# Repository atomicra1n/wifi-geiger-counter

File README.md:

# Wi-Fi Geiger Counter

A DIY Geiger counter PCB which can detect ionizing radiation and log readings over Wi-Fi. Built with an ESP32, and a HV multiplier circuit that steps up 3.7V to 400V for the GM tube.

## Features

- M4011/SBM-20 Geiger tube with pulse detection (tuned for M4011)
- Custom HV circuit (around 400V) with a single LiPo cell
- Wi-Fi data logging with a dashboard and a JSON API
- Buzzer with clicking on each count
- USB-C charging
- ESD and overvoltage protection

## Motivation
I made this project as I already own a FNIRSI GC-01 Geiger Counter, but I've always been intrigued by how they work and wanted to have a crack at making my own. It was an interesting challenge, especially given the difficulties around handling 400 volts, clearance, etc. Additionally, given the addition of Wi-Fi compared to the GC-01, I can log data from anywhere (the GC-01 requires a constant USB-C connection).

## Functionality
- Power from USB-C goes into a TP4056 which charges the LiPo battery. An AP2112K reduces the voltage from the battery to 3.3V to be safe for the ESP32.
- ESP32 uses PWM on a MMBTA42 transistor which switches an inductor, it ramps up to 200V-ish and then a diode + capacitor voltage doubler ups that to around 400V.
- A 100Megaohm/220kiloohm resistor divider reduces the 400V down to around 0.88, which is read by the ESP32 via its ADC and PID in the firmware adjusts to continuously hold at 400V.
- When the M4011 tube detects decay, the pulse enters a transistor and it is turned into a 3.3V signal for the ESP32 which is counted and clicks the buzzer.
- The firmware tallies counts over 60 seconds to calculate a CPM and converts into micro Sv/h via the configured conversion factor. ESP32 hosts a small web page and a JSON endpoint.

## How it was made
This is my first project in KiCad, so I had to figure it out for the most part. I picked the parts on LCSC and imported them, sketched the HV circuit on paper and then built it step by step. A few issues I ran into:
- I configured net class patterns to keep HV clearance, but I misconfigured them (set to HV instead of /HV) and they were ignored. As such, when I thought I was done, none of my rules were actually checked.
- My USB TVS diode was wired the wrong way which would short VBUS. I swapped it for a bidirectional one.
- My status LED was backwards and improperly wired, so I changed it to stay high on boot.
- The USB-C connector was facing inside the board instead of outside, very easy mistake to make in the PCB editor! Had to rotate and reroute completely.
- The buzzer footprint didn't match my actual part, so I had to find the right one on LCSC and reimport it.
- The ADC reading was wrong by around 30% in the firmware, so I fixed it by using the calibrated ADC reading in MicroPython

## Tech stack
- KiCad for the PCB design
- MicroPython for the ESP32 firmware
- JLCPCB for the board and LCSC for parts

## Repo layout
- pcb/ contains the actual KiCad project
- pcb/gerbers contain the gerber and drill files
- pcb/cpl/ contains the component positions
- firmware/ contains the MicroPython code
- images/ contains a render of the PCB
- BOM.csv contains the parts list
- JOURNAL.md is the devlog

## Bill of materials

| Part | Qty | Source | Unit | Total |
|---|---|---|---|---|
| [PCB Manufacturing](https://jlcpcb.com) | 1 | JLCPCB | $4.00 | $4.00 |
| [ESP32-C3-MINI](https://www.lcsc.com/product-detail/C2838502.html) | 1 | LCSC | $3.06 | $3.06 |
| [TP4056-42-ESOP8](https://www.lcsc.com/product-detail/C16581.html) | 5 | LCSC | $0.19 | $0.95 |
| [AP2112K-3.3TRG1](https://www.lcsc.com/product-detail/C51118.html) | 5 | LCSC | $0.18 | $0.90 |
| [USBLC6-2SC6](https://www.lcsc.com/product-detail/C7519.html) | 5 | LCSC | $0.18 | $0.90 |
| [MMBTA42](https://www.lcsc.com/product-detail/C94389.html) | 10 | LCSC | $0.05 | $0.50 |
| [MMBT3904](https://www.lcsc.com/product-detail/C242260.html) | 20 | LCSC | $0.04 | $0.80 |
| [US1M](https://www.lcsc.com/product-detail/C81191.html) | 3 | LCSC | $0.05 | $0.15 |
| [1N4148W](https://www.lcsc.com/product-detail/C917030.html) | 50 | LCSC | $0.01 | $0.50 |
| [SMF5.0CA](https://www.lcsc.com/product-detail/C908214.html) | 20 | LCSC | $0.02 | $0.40 |
| [MM3Z3V3](https://www.lcsc.com/product-detail/C52056.html) | 50 | LCSC | $0.02 | $1.00 |
| [Red LED 0805](https://www.lcsc.com/product-detail/C84256.html) | 50 | LCSC | $0.02 | $1.00 |
| [Yellow LED 0805](https://www.lcsc.com/product-detail/C84261.html) | 20 | LCSC | $0.02 | $0.40 |
| [MLT-8530](https://www.lcsc.com/product-detail/C94599.html) | 5 | LCSC | $0.21 | $1.05 |
| [FNR6045S103KT](https://www.lcsc.com/product-detail/C168108.html) | 5 | LCSC | $0.25 | $1.25 |
| [TYPE-C-31-M-12](https://www.lcsc.com/product-detail/C165948.html) | 5 | LCSC | $0.18 | $0.90 |
| [S2B-PH-K-S-GW](https://www.lcsc.com/product-detail/C157932.html) | 5 | LCSC | $0.17 | $0.85 |
| [1k 0805](https://www.lcsc.com/product-detail/C17513.html) | 100 | LCSC | $0.01 | $1.00 |
| [10k 0805](https://www.lcsc.com/product-detail/C17414.html) | 100 | LCSC | $0.01 | $1.00 |
| [5.1k 0805](https://www.lcsc.com/product-detail/C27834.html) | 100 | LCSC | $0.01 | $1.00 |
| [2.2k 0805](https://www.lcsc.com/product-detail/C17520.html) | 100 | LCSC | $0.01 | $1.00 |
| [220k 0805](https://www.lcsc.com/product-detail/C17556.html) | 100 | LCSC | $0.01 | $1.00 |
| [100k 0805](https://www.lcsc.com/product-detail/C17407.html) | 100 | LCSC | $0.01 | $1.00 |
| [4.7M 1206 500V](https://www.lcsc.com/product-detail/C510138.html) | 10 | LCSC | $0.01 | $0.10 |
| [10M 1206](https://www.lcsc.com/product-detail/C2933576.html) | 100 | LCSC | $0.01 | $1.00 |
| [10µF 0805](https://www.lcsc.com/product-detail/C15850.html) | 20 | LCSC | $0.07 | $1.40 |
| [1µF 0805](https://www.lcsc.com/product-detail/C28323.html) | 10 | LCSC | $0.04 | $0.40 |
| [100nF 0805](https://www.lcsc.com/product-detail/C49678.html) | 20 | LCSC | $0.02 | $0.40 |
| [10nF 1kV 1206](https://www.lcsc.com/product-detail/C107192.html) | 20 | LCSC | $0.03 | $0.60 |
| [GM Tube - M4011](https://github.com/SensorsIot/Geiger-Counter-RadiationD-v1.1-CAJOE-/blob/master/M4011%20Geiger%20Tube%20Specification.pdf) | 1 | Salvaged (FNIRSI GC-01) | $0.01 | $0.01 |
| 3.7V LiPo battery | 1 | Salvaged (FNIRSI GC-01) | $0.01 | $0.01 |
| [2.54-1*3P](https://www.lcsc.com/product-detail/C49257.html) | 20 | LCSC | $0.03 | $0.60 |
| **Parts subtotal** | | | | **$29.13** |
| Shipping (estimate) | | | | $25.00 |
| **Total** | | | | **$54.13** |

The Geiger Tube and Battery were salvaged from my GC-01, so they're effectively free. You can buy similar pieces on Ebay, Aliexpress or other stores.

## Assembly
Please keep in mind the board makes around 400V, even though it's low current, it could still inflict a shock, as such, please be careful. Before touching the HV side, I recommend unplugging the USB and battery and shorting C10 to GND to discharge it.

1. Order the PCB from JLCPCB using the gerber files and the parts from LCSC using the BOM.
2. Start with the power section. Solder the USB-C connector, USBLC6, TVS diode, TP4056, AP2112K and their resistors + capacitors. Do not work with the battery yet. Plug in USB-C and verify that the charge LED turns on. You should be getting 3.3V.
3. Solder the ESP32-C3-MINI-1 and the status LED. The ESP32 has pads underneath, so you'll need hot air or a hot plate for it. Flash MicroPython (more below) and check that you get a REPL on the ESP32.
4. Begin the HV supply. Solder Q1, L1, US1M diodes, 10nF 1kV capacitors and the 10 megaohm resistor divider chain but avoid connecting the tube at this point. Run the firmware and see the HV values it prints. I recommend not trying to measure the 400V with a multimeter as the 10 megaohm input can load the circuit.
5. Now for the pulse detection and the buzzer, solder Q2, Q3, the buzzer and the rest.
6. To finish, you can plug your tube into J3 (verify anode and cathode!!!) and connect the battery.

Keep in mind I intentionally avoid populating SW1 (reset) and SW2 (boot) switches for simplicity, but you may do so yourself if you want to (they're excluded from the BOM). If you ever need them, you can short their pads. The ESP32 can be flashed over USB without requiring the boot switch, as you can see below.

## Firmware

1. Start by downloading MicroPython for the ESP32-C3 from [micropython.org](https://micropython.org/download/ESP32_GENERIC_C3/) and flash it:
```sh
pip install esptool
esptool.py --chip esp32c3 erase_flash
esptool.py --chip esp32c3 write_flash -z 0x0 ESP32_GENERIC_C3-<your_version>.bin
```
2. Put your Wi-Fi name and password in firmware/config.py
3. Copy the files over:
```sh
pip install mpremote
cd firmware
mpremote cp config.py geiger.py hv_control.py buzzer.py wifi_manager.py main.py :
mpremote reset
```
4. If all goes well, your IP address should get printed over serial. Try opening it in the browser for the dashboard, or use /api/data for the JSON data.

## AI disclosure
LLMs (Claude Opus 4.6/5.5) was mostly used to get feedback on the schematic, review parts of it, assist in fixing bugs and writing the dashboard in wifi_manager.py. It was also used for other tedious but simple tasks, such as adding the BOM to this README.

---

Built for [Hack Club Half Life](https://halflife.hackclub.com/) 
Week 1 (PCBs).

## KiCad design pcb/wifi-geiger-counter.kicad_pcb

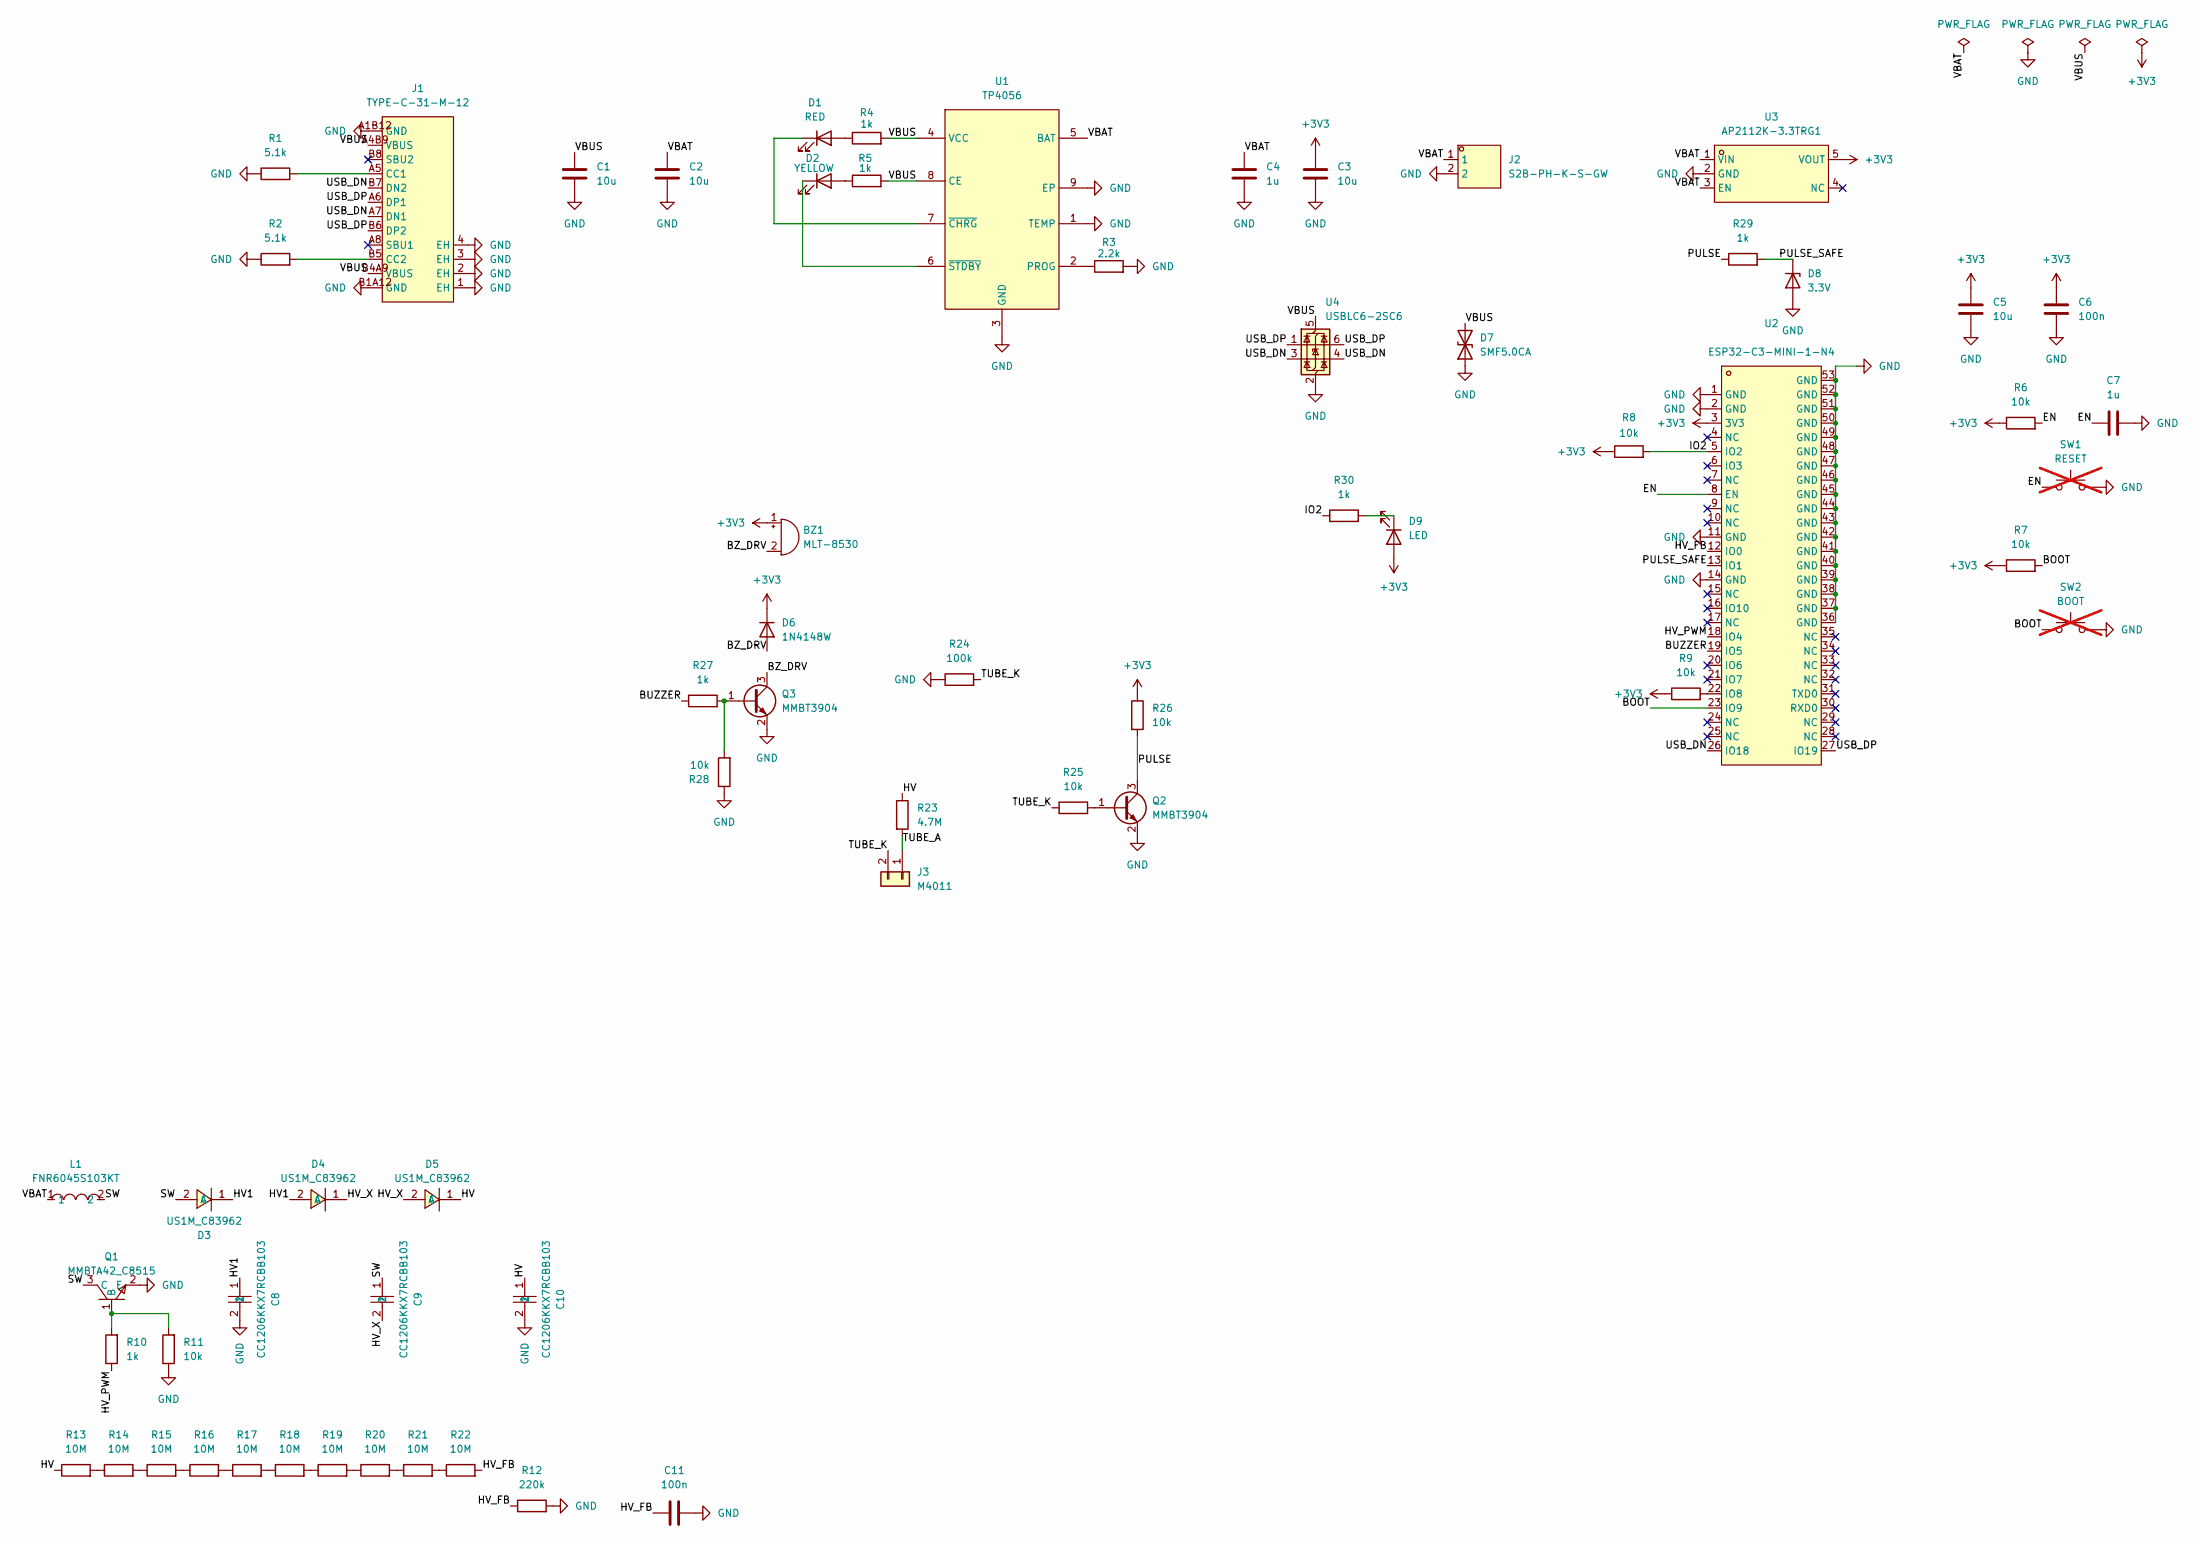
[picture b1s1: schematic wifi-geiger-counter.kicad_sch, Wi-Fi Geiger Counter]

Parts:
BZ1: MLT-8530; BUZ-SMD_4P-L8.5-W8.5-P8.50-BR
C1, C2, C3, C5: 10u; C_0805_2012Metric
C4, C7: 1u; C_0805_2012Metric
C6, C11: 100n; C_0805_2012Metric
C8, C9, C10: CC1206KKX7RCBB103; C1206; MPN CC1206KKX7RCBB103; LCSC Part C107192
D1: RED; LED_0805_2012Metric
D2: YELLOW; LED_0805_2012Metric
D3, D4, D5: US1M_C83962; SMA_L4.3-W2.6-LS5.2-RD; MPN US1M; LCSC Part C83962
D6: 1N4148W; D_SOD-123
D7: SMF5.0CA; D_SOD-123F
D8: 3.3V; D_SOD-323
D9: LED; LED_0805_2012Metric
J1: TYPE-C-31-M-12; USB-C_SMD-TYPE-C-31-M-12_1; MPN TYPE-C-31-M-12; LCSC Part C165948
J2: S2B-PH-K-S-GW; CONN-TH_S2B-PH-K-S-GW; MPN S2B-PH-K-S-GW; LCSC Part C157932
J3: M4011; PinHeader_1x02_P2.54mm_Vertical
L1: FNR6045S103KT; IND-SMD_L6.0-W6.0_FNR60XXS; MPN FNR6045S103KT; LCSC Part C168108
Q1: MMBTA42_C8515; SOT-23-3_L2.9-W1.3-P1.90-LS2.4-BR; MPN MMBTA42(RANGE:100-200); LCSC Part C8515
Q2, Q3: MMBT3904; SOT-23
R1, R2: 5.1k; R_0805_2012Metric
R3: 2.2k; R_0805_2012Metric
R4, R5, R10, R27, R29, R30: 1k; R_0805_2012Metric
R6, R7, R8, R9, R11, R25, R26, R28: 10k; R_0805_2012Metric
R12: 220k; R_0805_2012Metric
R13, R14, R15, R16, R17, R18, R19, R20, R21, R22: 10M; R_1206_3216Metric
R23: 4.7M; R_1206_3216Metric
R24: 100k; R_0805_2012Metric
SW1: RESET; SW_SPST_CK_KMS2xxGP; not fitted
SW2: BOOT; SW_SPST_CK_KMS2xxGP; not fitted
U1: TP4056; ESOP-8_L4.9-W3.9-P1.27-LS6.0-BL-EP; MPN TP4056-42-ESOP8; LCSC Part C16581
U2: ESP32-C3-MINI-1-N4; WIFIM-SMD_ESP32-C3-MINI-1; MPN ESP32-C3-MINI-1-N4; LCSC Part C2838502
U3: AP2112K-3.3TRG1; SOT-25-5_L2.9-W1.6-P0.95-LS2.8-BL; MPN AP2112K-3.3TRG1; LCSC Part C51118
U4: USBLC6-2SC6; SOT-23-6

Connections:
+3V3: BZ1.1 (+), C3.1, C5.1, C6.1, D6.1 (K), D9.2 (A), R6.1, R7.1, R8.1, R9.1, R26.1, U2.3 (3V3), U3.5 (VOUT)
/BOOT: R7.2, SW2.1, U2.23 (IO9)
/BUZZER: R27.1, U2.19 (IO5)
/BZ_DRV: BZ1.2 (-), D6.2 (A), Q3.3 (C)
/EN: C7.2, R6.2, SW1.1, U2.8 (EN)
/HV: C10.1, D5.1 (C), R13.1, R23.1
/HV1: C8.1, D3.1 (C), D4.2 (A)
/HV_FB: C11.1, R12.1, R22.2, U2.12 (IO0)
/HV_PWM: R10.1, U2.18 (IO4)
/HV_X: C9.2, D4.1 (C), D5.2 (A)
/IO2: R8.2, R30.1, U2.5 (IO2)
/PULSE: Q2.3 (C), R26.2, R29.1
/PULSE_SAFE: D8.1 (K), R29.2, U2.13 (IO1)
/SW: C9.1, D3.2 (A), L1.2, Q1.3 (C)
/TUBE_A: J3.1, R23.2
/TUBE_K: J3.2, R24.2, R25.1
/USB_DN: J1.A7 (DN1), J1.B7 (DN2), U2.26 (IO18), U4.3 (I/O2), U4.4 (I/O2)
/USB_DP: J1.A6 (DP1), J1.B6 (DP2), U2.27 (IO19), U4.1 (I/O1), U4.6 (I/O1)
/VBAT: C2.1, C4.1, J2.1, L1.1, U1.5 (BAT), U3.1 (VIN), U3.3 (EN)
/VBUS: C1.2, D7.2 (A2), J1.A4B9 (VBUS), J1.B4A9 (VBUS), R4.2, R5.2, U1.4 (VCC), U1.8 (CE), U4.5 (VBUS)
GND: C1.1, C2.2, C3.2, C4.2, C5.2, C6.2, C7.1, C8.2, C10.2, C11.2, D7.1 (A1), D8.2 (A), J1.1 (EH), J1.2 (EH), J1.3 (EH), J1.4 (EH), J1.A1B12 (GND), J1.B1A12 (GND), J2.2, Q1.2 (E), Q2.2 (E), Q3.2 (E), R1.1, R2.1, R3.2, R11.1, R12.2, R24.1, R28.1, SW1.2, SW2.2, U1.1 (TEMP), U1.3 (GND), U1.9 (EP), U2.1 (GND), U2.2 (GND), U2.11 (GND), U2.14 (GND), U2.36 (GND), U2.37 (GND), U2.38 (GND), U2.39 (GND), U2.40 (GND), U2.41 (GND), U2.42 (GND), U2.43 (GND), U2.44 (GND), U2.45 (GND), U2.46 (GND), U2.47 (GND), U2.48 (GND), U2.49 (GND), U2.50 (GND), U2.51 (GND), U2.52 (GND), U2.53 (GND), U3.2 (GND), U4.2 (GND)
unnamed: D1.2 (A), R4.1
unnamed: D1.1 (K), U1.7 (~CHRG)
unnamed: D2.2 (A), R5.1
unnamed: D2.1 (K), U1.6 (~STDBY)
unnamed: D9.1 (K), R30.2
unnamed: J1.A5 (CC1), R1.2
unnamed: J1.B5 (CC2), R2.2
unnamed: Q1.1 (B), R10.2, R11.2
unnamed: Q2.1 (B), R25.2
unnamed: Q3.1 (B), R27.2, R28.2
unnamed: R13.2, R14.1
unnamed: R14.2, R15.1
unnamed: R15.2, R16.1
unnamed: R16.2, R17.1
unnamed: R17.2, R18.1
unnamed: R18.2, R19.1
unnamed: R19.2, R20.1
unnamed: R20.2, R21.1
unnamed: R21.2, R22.1
unnamed: R3.1, U1.2 (PROG)
unnamed: R9.2, U2.22 (IO8)

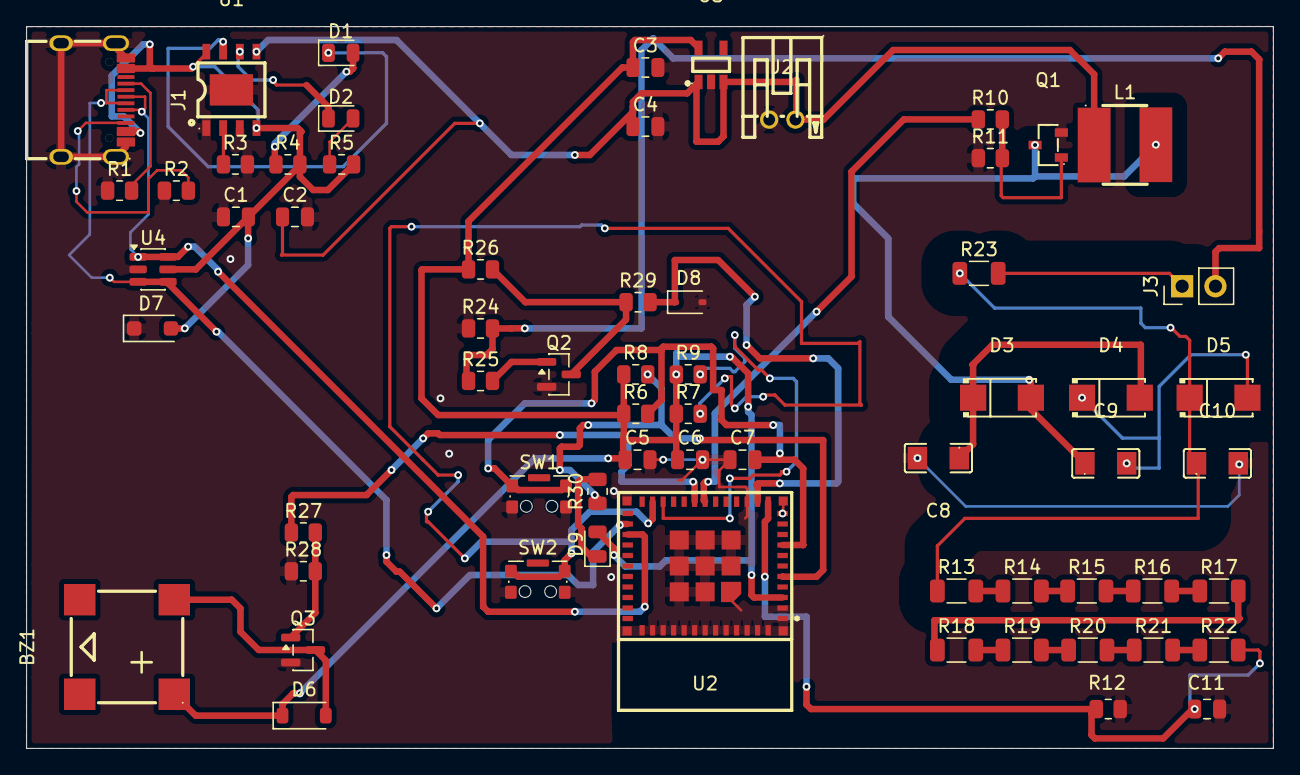
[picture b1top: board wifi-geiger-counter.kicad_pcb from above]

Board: 2 copper layers, 95.0 x 55.0 mm, 64 parts (0 on the bottom side), 42 nets.

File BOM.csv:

Item,Qty,Supplier,Cost/item,Total Cost,link
PCB Manufacturing,1,JLCPCB,$4.00,$4.00,https://jlcpcb.com
EPS32-C3-MINI,1,LCSC,$3.06,$3.06,https://www.lcsc.com/product-detail/C2838502.html
TP4056-42-ESOP8,5,LCSC,$0.19,$0.95,https://www.lcsc.com/product-detail/C16581.html
AP2112K-3.3TRG1,5,LCSC,$0.18,$0.90,https://www.lcsc.com/product-detail/C51118.html
USBLC6-2SC6,5,LCSC,$0.18,$0.90,https://www.lcsc.com/product-detail/C7519.html
MMBTA42,10,LCSC,$0.05,$0.50,https://www.lcsc.com/product-detail/C94389.html
MMBT3904,20,LCSC,$0.04,$0.80,https://www.lcsc.com/product-detail/C242260.html
US1M,3,LCSC,$0.05,$0.15,https://www.lcsc.com/product-detail/C81191.html
1N4148W,50,LCSC,$0.01,$0.50,https://www.lcsc.com/product-detail/C917030.html
SMF5.0A,5,LCSC,$0.13,$0.65,https://www.lcsc.com/product-detail/C151296.html
MM3Z3V3,50,LCSC,$0.02,$1.00,https://www.lcsc.com/product-detail/C52056.html
Red LED 0805,50,LCSC,$0.02,$1.00,https://www.lcsc.com/product-detail/C84256.html
Yellow LED 0805,20,LCSC,$0.02,$0.40,https://www.lcsc.com/product-detail/C84261.html
MLT-8530,5,LCSC,$0.21,$1.05,https://www.lcsc.com/product-detail/C94599.html
FNR6045S103KT,5,LCSC,$0.25,$1.25,https://www.lcsc.com/product-detail/C168108.html
TYPE-C-31-M-12,5,LCSC,$0.18,$0.90,https://www.lcsc.com/product-detail/C165948.html
S2B-PH-K-S-GW,5,LCSC,$0.17,$0.85,https://www.lcsc.com/product-detail/C157932.html
1k 0805,100,LCSC,$0.01,$1.00,https://www.lcsc.com/product-detail/C17513.html
10k 0805,100,LCSC,$0.01,$1.00,https://www.lcsc.com/product-detail/C17414.html
5.1k 0805,100,LCSC,$0.01,$1.00,https://www.lcsc.com/product-detail/C27834.html
2.2k 0805,100,LCSC,$0.01,$1.00,https://www.lcsc.com/product-detail/C17520.html
220k 0805,100,LCSC,$0.01,$1.00,https://www.lcsc.com/product-detail/C17556.html
100k 0805,100,LCSC,$0.01,$1.00,https://www.lcsc.com/product-detail/C17407.html
4.7M 1206 500V,10,LCSC,$0.01,$0.10,https://www.lcsc.com/product-detail/C510138.html
10M 1206,100,LCSC,$0.01,$1.00,https://www.lcsc.com/product-detail/C2933576.html
10µF 0805,20,LCSC,$0.07,$1.40,https://www.lcsc.com/product-detail/C15850.html
1µF 0805,10,LCSC,$0.04,$0.40,https://www.lcsc.com/product-detail/C28323.html
100nF 0805,20,LCSC,$0.02,$0.40,https://www.lcsc.com/product-detail/C49678.html
10nF 1kV 1206,20,LCSC,$0.03,$0.60,https://www.lcsc.com/product-detail/C107192.html
Tact switch,20,LCSC,$0.02,$0.40,https://www.lcsc.com/product-detail/C318884.html
GM Tube - M4011,1,Myself - Salvaged from FNIRSI GC-01,$0.01,$0.01,https://github.com/SensorsIot/Geiger-Counter-RadiationD-v1.1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
3.7V LiPo battery,1,Myself - Salvaged from FNIRSI GC-01,$0.01,$0.01,https://tipa.eu/en-en/products/rechargeable-battery-lipo-3-7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
2.54-1*3P,20,LCSC,$0.03,$0.60,https://www.lcsc.com/product-detail/C49257.html
Estimated total shipping,1,,,$25.00,

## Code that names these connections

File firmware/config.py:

# pin assignments
HV_PWM_PIN = 4
HV_FB_PIN = 0 
PULSE_PIN = 1
BUZZER_PIN = 5
LED_PIN = 2

# the feedback divider is 100M/220k so ratio is like 454.5
# 400v / 454.5 = 0.88v = 880mv on the adc
HV_TARGET = 880

# m4011 tube conversion factor
CPM_TO_USVH = 0.0066

WIFI_SSID = ""
WIFI_PASS = ""
